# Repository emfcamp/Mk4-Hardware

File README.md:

Hardware
========

Hardware for the TiLDA Mkδ Badge for [Electromagnetic Field
2018](https://www.emfcamp.org).

Key Specs
---------
* TBD
*
*

License
-------
Copyright Electromagnetic Field Ltd. 2017

This documentation describes Open Hardware and is licensed under the
CERN OHL v. 1.2.  You may redistribute and modify this documentation
under the terms of the CERN OHL v.1.2. (http://ohwr.org/cernohl or the
LICENSE file in this repository). This documentation is distributed
WITHOUT ANY EXPRESS OR IMPLIED WARRANTY, INCLUDING OF MERCHANTABILITY,
SATISFACTORY QUALITY AND FITNESS FOR A PARTICULAR PURPOSE. Please see
the CERN OHL v.1.2 for applicable conditions.

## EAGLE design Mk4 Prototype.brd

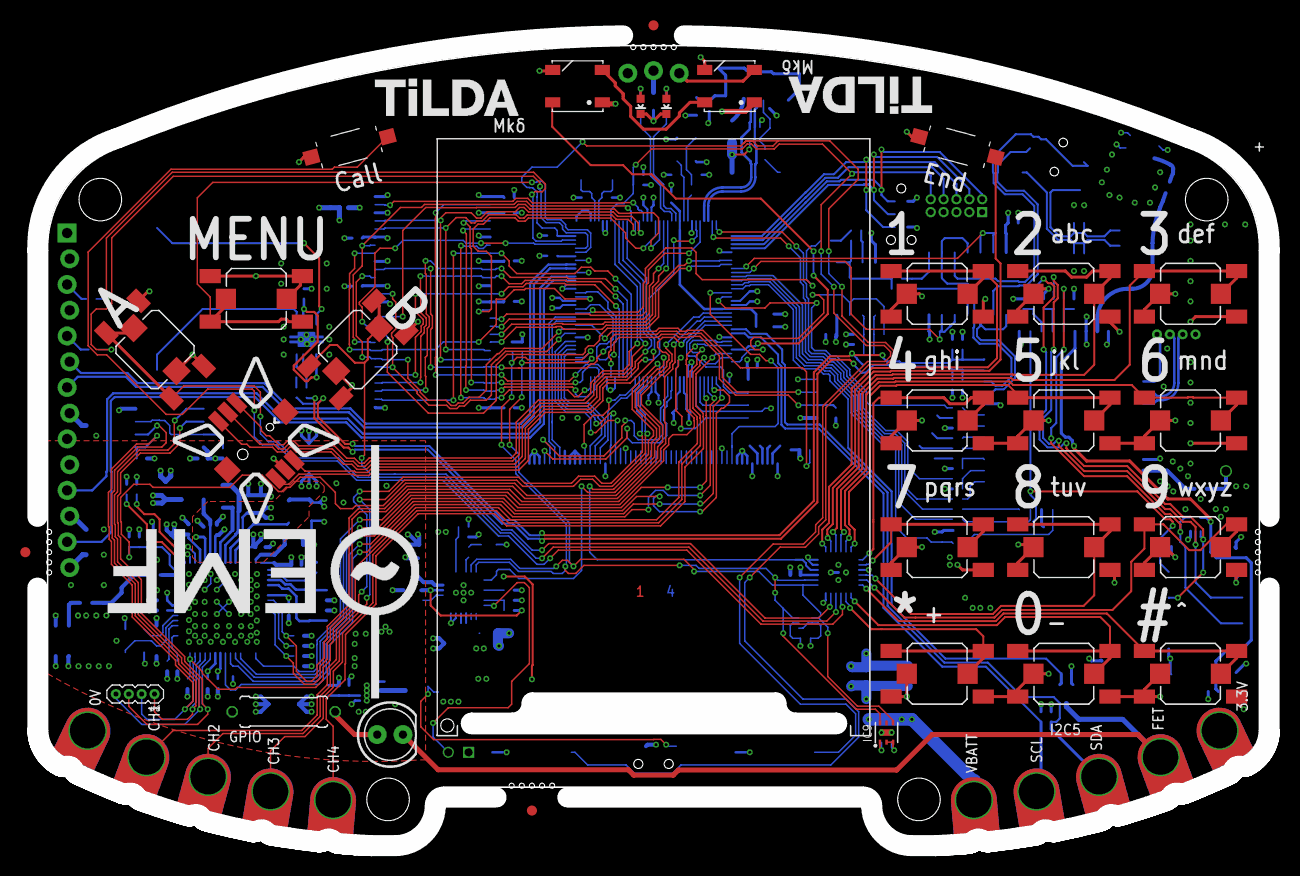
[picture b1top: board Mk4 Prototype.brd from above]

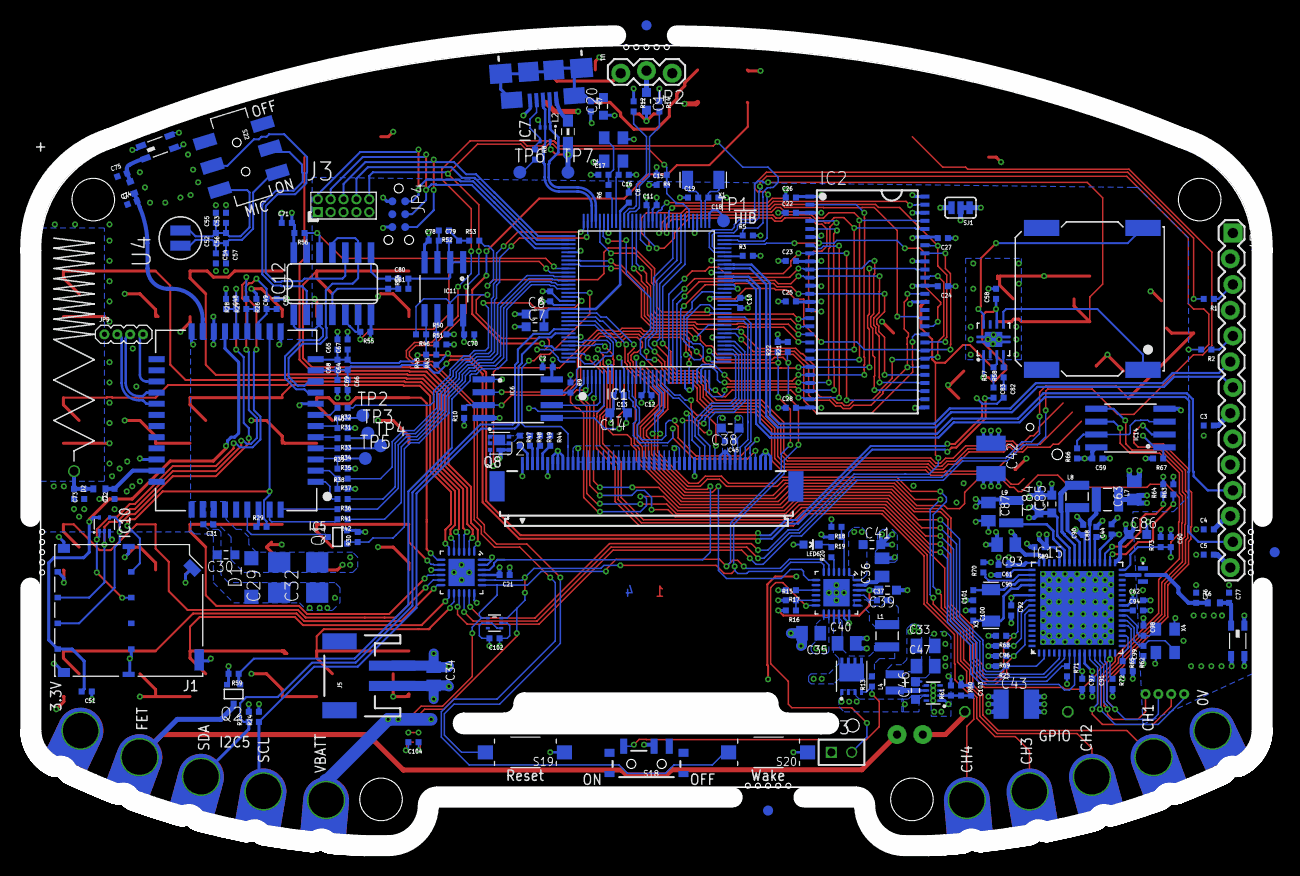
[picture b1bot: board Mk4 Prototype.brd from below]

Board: 4 copper layers, 121.6 x 80.0 mm, 278 parts (242 on the bottom side), 234 nets.

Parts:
ANT1, ANT2: 2450AT18D0100
ARTWORK1: ARTWORK_JOYSTICK; TILDA_ARTWORK_JOYSTICK
ARTWORK2: ARTWORK_KEYPAD; TILDA_ARTWORK_KEYPAD
BATT: 1000mAh JST-PH; BATTERY-32X50
C1, C7, C14, C41, C86: 0603/1u/6V3/X5R; C0603K-SMALL
C2, C3, C4, C5, C8, C9, C10, C11, C12, C13, C15, C21, C22, C23, C24, C25, C26, C27, C28, C31, C44, C45, C51, C58, C59, C60, C61, C62, C70, C71, C80, C81, C91, C92, C94, C95, C96, C97, C102, C104: 0402/100n/10V/X5R; C0402-SMALLER
C6: 0603/2u2/6V3/X5R; C0603K-SMALL
C16, C17, C18, C19, C98, C99, C100, C101: 0402/12p/50V/C0G; C0402-SMALLER
C20: 0603/3n3/50V/X7R; C0603K-SMALL
C29, C32: 1411/100u/10V/Tant; CT3528
C30, C38, C39, C46: 0603/4u7/10V/X5R; C0603K-SMALL
C33, C34, C35, C36, C40, C47, C63, C87, C93: 0805/10u/10V/X5R; C0805-N
C37: 0402/47n/10V/X5R; C0402-SMALLER
C42, C43: 1210/100u/6V3/X5R; C1210K
C48, C49, C50: 0402/22p/10V/C0G; C0402-SMALLER
C52, C54, C55, C64, C66, C67: 0402/33p/50V/C0G; C0402-SMALLER
C53, C56, C57, C65, C68, C69: 0402/10p/50V/C0G; C0402-SMALLER
C72, C73, C74, C75, C76, C77: C0402-SMALLER
C78: 0402/1n/10V/X5R; C0402-SMALLER
C79: 0402/2n2/10V/X5R; C0402-SMALLER
C82, C83: 0402/220n/6V/X5R; C0402-SMALLER
C84, C85: 0603/22u/4V/X5R; C0603K-SMALL
C88, C89, C90: 0402/4u7/6V3/X5R; C0402-SMALLER
C103: 0402/120p/50V/C0G; C0402-SMALLER
D1: MMSZ5231BT1G; SOD123
D2: LXES15AAA1-153; R0402-SMALLER
FID1, FID2, FID3, FID4, FID5, FID6: FIDUCIAL1X2.5-STOP; FIDUCIAL-1X2.5-STOP
FL1: DEA202450BT-1294C1-H; DEA202450BT
IC1: MSP432E401; QFP128-0.4
IC2: AS4C4M16SA-7TCN; TSOP54-400
IC3: TPS62822DLCR; VSON-HR
IC4: TCA9555RGER; QFN-24
IC5: SIM800C
IC6: SST26VF016B-104I/SM; SO08-EIAJ
IC7, IC10: TPD3E001DRL; DRL-5
IC8: BQ25601; QFN-24
IC9: OPT3001; USON-6
IC11: LMV358ID; SO08
IC12: SN74HC4066D; SO14
IC13: TPA2006D1; VSON-8
IC14: MX25R1635FM1IL0; SO08-EIAJ
IC15: CC3120R; VQFN-64
J1: 78723-1001; MSIM-MOLEX-LWK
J2: ER-CON50HT-1; FH12-50S-0.5SH
J3: 2x5 1.27mm; PINHEAD_2X05_127
J4: GSM-COIL-ANT; GSM-ANTENNA
J5: S2B-PH-SM4-TB(LF)(SN); JST-2-SMD
JP2: 1x03; 1X03_LOCK
JP3: 1x02 2MM; 1X02_2MM
JP4: TC2030-MCP-NL
JP7: 1x14; 1X14_LOCK
JP8, JP9: 1x04_1.27MM; 1X04-1.27MM
L1: SRN2512-2R2M; 1008
L2: BLM18KG121TN1D; WUERTH-0805
L3, L5, L6: 0402/0R/5%; L0402
L4: DFE201610E-R47M=P2; 0806
L7, L9: LQM2HPN2R2MG0L; 1008
L8: LQM2HPN1R0MG0L; 1008
LAYERS1: LAYER_NUMBRS_4_SMALL; LAYER_NUMBERS_4_SMALL
LCD: ER-TFT024-3
LED1, LED2: WS2812B
LED3, LED6: 0603 RED; LED-0603-CORRECT
LED4: 0603 GREEN; LED-0603-CORRECT
LED5: LED 5MM; LED5MM
LOGO1: EMFLOGO-BOTH; EMFLOGO
PCB: TiLDA Mk4 PCB; TILDA_MK4_OUTLINE
Q1, Q2: 2N7002PW; SC70-3-R
Q3: CSD25402Q3A; Q3A
Q8: CSD13202Q2; Q2
R1, R2, R31, R32, R33, R34, R35, R36, R37, R41, R42: 0402/1K/5%; R0402-SMALLER
R3: 0402/4K87/5%; R0402-SMALLER
R4, R9, R10, R13, R15, R16, R18, R19, R20, R43, R45, R46, R54, R55, R56, R59, R62, R66: 0402/10K/5%; R0402-SMALLER
R5, R7: 0402/1M/5%; R0402-SMALLER
R6, R12, R17: 0402/2K/5%; R0402-SMALLER
R8: 0402/100R/5%; R0402-SMALLER
R11: 0309/10
R14, R21, R22, R23, R24, R29: 0402/4K7/5%; R0402-SMALLER
R25, R30, R63, R64, R65, R67, R68, R69, R70, R71, R72, R73: 0402/100K/5%; R0402-SMALLER
R26, R27, R28: 0402/51R/5%; R0402-SMALLER
R38, R39, R40: 0402/5K6/5%; R0402-SMALLER
R44, R47, R48, R49: 0402/12R/5%; R0402-SMALLER
R50, R51: 0402/22K/5%; R0402-SMALLER
R52: 0402/14K7/5%; R0402-SMALLER
R53: 0402/7K87/5%; R0402-SMALLER
R57, R58: 0402/150K/1%; R0402-SMALLER
R60: 0402/732K/5%; R0402-SMALLER
R61: 0402/162K/5%; R0402-SMALLER
S1, S2, S3, S4, S5, S6, S7, S8, S9, S10, S11, S12, S13, S14, S15: SKPMAPE010; SKPMAPE010-COMBINED
S16, S17, S19, S20: 3X6X2.5; TACTILE_SWITCH_SMD_3X6X2.5H
S18: CUS-12TB; SWITCH-SPST-SMD-A
S22: AYZ0202AGRLC; AYZ-JS-COMBINED
SJ1: Amp Power Select; SJ_3
SW1: JOYSTICK; JOYSTICK_MULTICOMP_NOSILK
TP1, TP2, TP3, TP4, TP5, TP6, TP7: TP; B1,27
U1: ZX62-B-5PA(33); USB-AB-MICRO-SMD_LWK
U2: TMP102; SOT563
U4: MIC-4MM; MIC-SMD-4MM
U5: LDMS1540S-01-R8-0.8-R; SPEAKER-15MM-SMD
X1, X3: ABS07-32.768KHZ-T; RESONATOR_EPSON_FC_145
X2: ABM8G-25.000MHZ-B4Y-T; CRYSTAL-3.2-2.5
X4: ABM8-40.000MHZ-10-1-U-T; CRYSTAL-3.2-2.5

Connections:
3V3: C2.2, C3.2, C4.2, C9.2, C10.2, C11.2, C12.2, C13.2, C14.2, C21.2, C22.2, C23.2, C24.2, C25.2, C26.2, C27.2, C28.2, C33.1, C38.2, C42.2, C43.2, C45.2, C47.1, C59.2, C70.2, C71.2, C88.1, C89.1, C90.1, C91.1, C92.1, C93.1, C102.1, C103.1, C104.1, IC1.7, IC1.8, IC1.9, IC1.16, IC1.26, IC1.28, IC1.39, IC1.47, IC1.51, IC1.52, IC1.68, IC1.69, IC1.79, IC1.90, IC1.101, IC1.113, IC1.122, IC2.1, IC2.3, IC2.9, IC2.14, IC2.27, IC2.43, IC2.49, IC4.21, IC6.8, IC9.1, IC11.8, IC12.14, IC14.8, IC15.10, IC15.37, IC15.39, IC15.44, IC15.47, IC15.54, J2.1, J2.7, J2.8, J2.9, J2.35, J2.40, J2.41, J2.42, J3.1, JP4.1, JP7.8, JP7.12, L4.2, PCB.3V3, R4.2, R5.2, R9.1, R10.1, R11.2, R21.2, R22.2, R23.2, R24.2, R50.2, R56.2, R60.1, R66.1, R67.2, R68.2, R69.2, R73.2, SJ1.1, SW1.COM, U2.5
3V3_POE: C5.2, JP7.14
!HIB: IC1.65, TP1.TP
!RESET: C15.2, IC1.70, J3.10, R4.1, S19.2
!WAKE: IC1.64, R5.1, S20.2
AIN0_ADC_X: IC1.13, J2.46
AIN1_ADC_Y: IC1.12, J2.47
AIN4_SPK_ADC: IC1.128, IC11.7, R46.2
AIN5_CH3: IC1.127, PCB.CH2
AMP_IN_N: IC13.4, R58.2
AMP_IN_P: IC13.3, R57.2
AMP_IN_R_N: C82.1, R58.1
AMP_IN_R_P: C83.1, R57.1
AMP_VDD: C58.1, IC13.1, IC13.6, SJ1.2
BQ_!CE: IC8.9, R17.1
BQ_!INT: IC1.14, IC8.7
BQ_!QON: IC8.12, JP3.2
BQ_PMID: C36.1, IC8.23
BQ_PSEL: IC8.2, R18.1, R19.1
BQ_REGN: C39.2, IC8.22, R16.2
BQ_STAT: IC8.4, R20.1
BQ_STAT_R: LED6.C, R20.2
BQ_SW: C37.2, IC8.19, IC8.20, L1.1
BQ_TS: IC8.11, R15.2, R16.1
BTN_1: IC4.1, S1.2, S1.B1, S1.B2
BTN_2: IC4.3, S2.2, S2.B1, S2.B2
BTN_3: IC4.4, S3.2, S3.B1, S3.B2
BTN_4: IC4.7, S4.2, S4.B1, S4.B2
BTN_5: IC4.6, S5.2, S5.B1, S5.B2
BTN_6: IC4.5, S6.2, S6.B1, S6.B2
BTN_7: IC4.8, S7.2, S7.B1, S7.B2
BTN_8: IC4.10, S8.2, S8.B1, S8.B2
BTN_9: IC4.11, S9.2, S9.B1, S9.B2
BTN_10: IC4.14, S10.2, S10.B1, S10.B2
BTN_11: IC4.13, S11.2, S11.B1, S11.B2
BTN_12: IC4.12, S12.2, S12.B1, S12.B2
BTN_A: IC4.16, S13.2, S13.B1, S13.B2
BTN_B: IC4.17, S15.2, S15.B1, S15.B2
BTN_CALL: IC4.15, S16.2
BTN_END: IC4.2, S17.2
BTN_MENU: IC1.60, S14.2, S14.B1, S14.B2
BTST: C37.1, IC8.21
BT_ANT: C74.2, IC5.20, L5.1
BT_ANT_L: ANT2.1, C75.2, L5.2
CC_!HIB: IC1.124, IC15.2, R25.1
CC_!RESET: C60.2, IC1.118, IC15.32, R73.1
CC_!RTS: IC15.50, R70.1
CC_IRQ: IC1.123, IC15.15, R72.1
CC_RCT_XTAL_N: C100.2, IC15.52, X3.P$1
CC_RESERVED@19: IC15.19, R65.1
CC_RTC_XTAL_P: C101.2, IC15.51, X3.P$2
CC_WLAN_XTAL_: C99.2, IC15.22, X4.3
CC_WLAN_XTAL_P: C98.2, IC15.23, X4.1
CH4: IC1.126, PCB.CH1
DCDC_ANA_SW: IC15.38, L7.2
DCDC_DIG_SW: IC15.43, L9.2
DCDC_PA_SW_N: IC15.41, L8.1
DCDC_PA_SW_P: IC15.40, L8.2
EN0RXI_N: IC1.53, JP7.13
EN0RXI_P: IC1.54, JP7.11
EN0TXO_N: IC1.56, JP7.7
EN0TXO_P: IC1.57, JP7.6
ETHLED0: IC1.63, R1.2
ETHLED0_R: JP7.3, R1.1
ETHLED1: IC1.61, R2.2
ETHLED1_R: JP7.5, R2.1
FET: IC1.110, Q2.1, R59.1
FET_OUT: LED5.K, PCB.FET, Q2.3
FLASH_!CS: IC14.1, IC15.14, JP8.2, R67.1
FLASH_CLK: IC14.6, IC15.11, JP8.3
FLASH_MISO: IC14.2, IC15.13, JP8.1
FLASH_MOSI: IC14.5, IC15.12, JP8.4
FLASH_PU: IC14.3, IC14.7, R66.2
GMS_ANT_L: C73.2, D2.1, J4.ANT, L3.2
GND: ANT1.2, ANT1.3, ANT1.4, ANT2.2, ANT2.3, ANT2.4, C1.2, C2.1, C3.1, C4.1, C5.1, C6.1, C7.1, C8.1, C9.1, C10.1, C11.1, C12.1, C13.1, C14.1, C15.1, C16.1, C17.1, C18.1, C19.1, C20.1, C21.1, C22.1, C23.1, C24.1, C25.1, C26.1, C27.1, C28.1, C29.-, C30.1, C31.1, C32.-, C33.2, C34.2, C35.2, C36.2, C38.1, C39.1, C40.2, C41.2, C42.1, C43.1, C44.2, C45.1, C46.2, C47.2, C48.1, C49.1, C50.1, C51.1, C53.2, C54.2, C55.2, C57.2, C58.2, C59.1, C60.1, C61.2, C62.2, C63.2, C65.2, C66.2, C67.2, C69.2, C70.1, C71.1, C72.1, C73.1, C74.1, C75.1, C76.1, C77.1, C78.1, C84.2, C85.2, C86.2, C87.2, C88.2, C89.2, C90.2, C91.2, C92.2, C93.2, C94.2, C95.2, C96.2, C97.2, C98.1, C99.1, C100.1, C101.1, C102.2, C104.2, D1.A, D2.2, FL1.GND@2, FL1.GND@4, IC1.10, IC1.17, IC1.48, IC1.55, IC1.58, IC1.80, IC1.114, IC2.6, IC2.12, IC2.28, IC2.41, IC2.46, IC2.52, IC2.54, IC3.3, IC3.5, IC4.9, IC4.18, IC4.23, IC4.24, IC4.25, IC5.8, IC5.13, IC5.19, IC5.21, IC5.27, IC5.30, IC5.31, IC5.33, IC5.36, IC5.37, IC6.4, IC7.3, IC8.17, IC8.18, IC8.25, IC9.2, IC9.3, IC9.PAD, IC10.3, IC11.4, IC12.7, IC13.7, IC13.PAD, IC14.4, IC15.PAD, J1.C4, J1.C5, J1.GND1, J1.GND2, J1.GND3, J1.GND4, J1.GND5, J1.GND6, J2.6, J2.11, J2.12, J2.13, J2.14, J2.15, J2.16, J2.17, J2.18, J2.19, J2.20, J2.21, J2.22, J2.23, J2.24, J2.25, J2.26, J2.27, J2.28, J2.29, J2.30, J2.31, J2.32, J2.43, J2.48, J2.49, J2.50, J3.3, J3.5, J3.9, J5.1, JP2.1, JP3.1, JP4.5, JP7.1, JP7.2, JP7.4, JP9.1, LED1.3, LED2.3, LED3.C, LED4.C, PCB.GND, Q1.2, Q2.2, Q8.4, Q8.EP2, R3.2, R7.2, R15.1, R17.2, R19.2, R25.2, R30.2, R38.2, R39.2, R40.2, R51.2, R55.1, R59.2, R61.2, R62.2, R63.2, R64.2, R65.2, R70.2, R71.2, R72.2, S1.1, S1.A1, S1.A2, S2.1, S2.A1, S2.A2, S3.1, S3.A1, S3.A2, S4.1, S4.A1, S4.A2, S5.1, S5.A1, S5.A2, S6.1, S6.A1, S6.A2, S7.1, S7.A1, S7.A2, S8.1, S8.A1, S8.A2, S9.1, S9.A1, S9.A2, S10.1, S10.A1, S10.A2, S11.1, S11.A1, S11.A2, S12.1, S12.A1, S12.A2, S13.1, S13.A1, S13.A2, S14.1, S14.A1, S14.A2, S15.1, S15.A1, S15.A2, S16.1, S17.1, S18.2, S19.1, S20.1, U1.GND, U2.2, U2.4, X2.2, X2.4, X4.2, X4.4
GSM_ANT: C72.2, IC5.32, L3.1
I2C5_EXT_SCL: IC1.121, PCB.SCL, R24.1
I2C5_EXT_SDA: IC1.120, PCB.SDA, R23.1
I2C9_SCL: IC1.33, IC4.19, IC8.5, IC9.4, R22.1, U2.1
I2C9_SDA: IC1.34, IC4.20, IC8.6, IC9.6, R21.1, U2.6
JOY_CEN: IC1.72, SW1.CTR
JOY_DOWN: IC1.74, SW1.D
JOY_LEFT: IC1.73, SW1.C
JOY_RIGHT: IC1.91, SW1.B
JOY_UP: IC1.71, SW1.A
LCD_!RST: IC1.111, J2.10
LCD_DCX: IC1.20, J2.36
LCD_TEAR: IC1.21, J2.39
LED1: IC1.86, R12.2
LED1_R: LED3.A, R12.1
LED2: IC1.85, R14.2
LED2_R: LED4.A, R14.1
LED5_R: LED5.A, R11.1
LEDK: Q8.1, Q8.2, Q8.5, Q8.6, Q8.EP1, R44.1, R47.1, R48.1, R49.1
LEDK1: J2.2, R47.2
LEDK2: J2.3, R48.2
LEDK3: J2.4, R49.2
LEDK4: J2.5, R44.2
MIC_MUX_N: IC5.10, IC12.9, IC12.11
MIC_MUX_P: IC5.9, IC12.1, IC12.3
MIC_N: C52.2, C53.1, C55.1, C56.2, S22.6, U4.-
MIC_P: C52.1, C54.1, C56.1, C57.1, S22.3, U4.+
MIC_PWM_AMP: C79.1, C80.2, C81.2, IC11.1, IC11.2
MIC_PWM_AMP_+: C78.2, IC11.3, R52.2
MIC_PWM_N: C80.1, IC12.8, R54.1
MIC_PWM_P: C81.1, IC12.4, R54.2
MIC_PWM_R: C79.2, R52.1, R53.1
MIC_SWITCHED_N: IC12.10, S22.5
MIC_SWITCHED_P: IC12.2, S22.2
MUX_A: IC1.105, IC12.12, IC12.13, R56.1
MUX_B: IC1.106, IC12.5, IC12.6, R55.2
NETLIGHT_R: IC5.41, R42.2
OSC0: C16.2, IC1.88, X2.1
OSC1: IC1.89, R6.1
OSC1_R: C17.2, R6.2, X2.3
POWER_SWITCH: Q3.4, R13.1, S18.3
PWM0_LCD_BLIGHT: IC1.42, Q8.3
PWM3_MIC_PWM: IC1.45, R53.2
PWR_KEY_FET: IC5.39, Q1.3
RBIAS+: IC1.59, R3.1
SDRAM_!CAS: IC1.83, IC2.17
SDRAM_!CS: IC1.103, IC2.19
SDRAM_!RAS: IC1.84, IC2.18
SDRAM_!WE: IC1.92, IC2.16
SDRAM_A0: IC1.29, IC2.2, IC2.23
SDRAM_A1: IC1.30, IC2.4, IC2.24
SDRAM_A2: IC1.31, IC2.5, IC2.25
SDRAM_A3: IC1.32, IC2.7, IC2.26
SDRAM_A4: IC1.22, IC2.8, IC2.29
SDRAM_A5: IC1.23, IC2.10, IC2.30
SDRAM_A6: IC1.24, IC2.11, IC2.31
SDRAM_A7: IC1.25, IC2.13, IC2.32
SDRAM_A8: IC1.40, IC2.33, IC2.42
SDRAM_A9: IC1.41, IC2.34, IC2.44
SDRAM_A10: IC1.50, IC2.22, IC2.45
SDRAM_A11: IC1.49, IC2.35, IC2.47
SDRAM_A12: IC1.75, IC2.36, IC2.48
SDRAM_BA0: IC1.76, IC2.20, IC2.50
SDRAM_BA1: IC1.77, IC2.21, IC2.51
SDRAM_CKE: IC1.104, IC2.37
SDRAM_CLK: IC1.62, IC2.38
SDRAM_D15: IC1.78, IC2.53
SDRAM_DQMH: IC1.82, IC2.39
SDRAM_DQML: IC1.81, IC2.15
SIM_CLK: IC10.2, J1.C3, R27.2
SIM_CLK_R: C49.2, IC5.16, R27.1
SIM_CTS: R34.1, TP4.TP
SIM_CTS_R: IC5.4, R34.2
SIM_DATA: IC10.1, J1.C7, R26.2
SIM_DATA_R: C50.2, IC5.15, R26.1
SIM_DCD: R33.1, TP3.TP
SIM_DCD_R: IC5.5, R33.2
SIM_DET: IC5.14, J1.C8, R29.2
SIM_DTR: R31.1, TP2.TP
SIM_DTR_R: IC5.6, R31.2, R40.1
SIM_D_N: IC5.26, JP9.2
SIM_D_P: IC5.25, JP9.3
SIM_NETLIGHT: IC1.108, R42.1
SIM_PWR_KEY: IC1.109, Q1.1, R30.1
SIM_RI_R: IC5.7, R32.2
SIM_RST: IC10.4, J1.C2, R28.2
SIM_RST_R: C48.2, IC5.17, R28.1
SIM_RTS: R35.1, TP5.TP
SIM_RTS_R: IC5.3, R35.2, R39.1
SIM_RXD_R: IC5.2, R37.2, R38.1
SIM_STATUS: IC1.107, R41.1
SIM_STATUS_R: IC5.42, R41.2
SIM_TXD_R: IC5.1, R36.2
SIM_VBUS: IC5.24, JP9.4
SIM_VDD: C51.2, IC5.18, IC10.5, J1.C1
SOP0: IC15.35, R64.1
SOP1: IC15.34, R63.1
SOP2: IC15.21, R62.1
SPK_AMP_N: IC13.8, U5.-
SPK_AMP_P: IC13.5, U5.+
SPK_N: C64.2, C65.1, C67.1, C68.2, C82.2, IC5.12, R43.1
SPK_P: C64.1, C66.1, C68.1, C69.1, C83.2, IC5.11, R45.1
SPK_R_N: IC11.5, R45.2, R46.1
SPK_R_P: IC11.6, R43.2, R50.1, R51.1
SSI0_LCD_CLK: IC1.35, J2.37
SSI0_LCD_CS: IC1.36, J2.38
SSI0_LCD_MISO: IC1.38, J2.33
SSI0_LCD_MOSI: IC1.37, J2.34
SSI2_CC_!CS: IC1.3, IC15.8
SSI2_CC_CLK: IC1.4, IC15.5
SSI2_CC_MISO: IC1.1, IC15.7, R71.1
SSI2_CC_MOSI: IC1.2, IC15.6
SSI3_CLK: IC1.5, IC6.6
SSI3_DAT0: IC1.11, IC6.5
SSI3_DAT1: IC1.27, IC6.2
SSI3_DAT2: IC1.46, IC6.3, R10.2
SSI3_DAT3: IC1.119, IC6.7, R9.2
SSI3_FSS: IC1.6, IC6.1
SW: IC3.6, L4.1
T3CCPO_WS2812: IC1.125, LED1.4
TCA_INT: IC1.15, IC4.22
TCK_SWCLK: IC1.100, J3.4, JP4.4
TDI: IC1.98, J3.8
TDO_SWO: IC1.97, J3.6, JP4.6
TMS_SWDIO: IC1.99, J3.2, JP4.2
TPS_FB: C103.2, IC3.2, R60.2, R61.1
T_X: IC1.43, J2.44
T_Y: IC1.44, J2.45
UART1_SIM_RI: IC1.112, R32.1
UART1_SIM_RX: IC1.95, R36.1
UART1_SIM_TX: IC1.96, R37.1
UART3_CC_RX: IC1.116, IC15.55, R68.1
UART3_CC_TX: IC1.117, IC15.57, R69.1
UART5_EXT_RX: IC1.18, PCB.CH3
UART5_EXT_TX: IC1.19, PCB.CH4
USB_D_N: IC1.93, IC7.1, U1.D-
USB_D_P: IC1.94, IC7.2, U1.D+
USB_ID: R8.2, TP6.TP
USB_ID_R: IC7.4, R8.1, U1.ID
USB_SHIELD: C20.2, R7.1, U1.SHIELD, U1.SHIELD@0, U1.SHIELD@1, U1.SHIELD@2, U1.SHIELD@3, U1.SHIELD@5
VBAT: C34.1, C35.1, IC8.13, IC8.14, J5.2
VBATT: C1.1, C29.+, C30.2, C31.2, C32.+, C46.1, D1.C, IC3.1, IC3.7, IC5.34, IC5.35, JP2.2, LED1.1, LED2.1, Q3.1, Q3.2, Q3.3, SJ1.3
VBUS: C41.1, IC7.5, IC8.1, IC8.24, L2.2, LED6.A, TP7.TP
VBUS_L: L2.1, U1.VBUS
VDDC: C6.2, C7.2, C8.2, IC1.87, IC1.115
VDD_ANA: C44.1, C61.1, C62.1, C63.1, IC15.25, IC15.36, IC15.48, L7.1
VDD_DIG_CC: C87.1, C96.1, C97.1, IC15.9, IC15.56, L9.1
VDD_EXT: IC5.40, R29.1
VDD_PA: C84.1, C85.1, C86.1, IC15.33, IC15.42
VDD_PLL: C94.1, IC15.24
VDD_RAM: C95.1, IC15.49
V_UNREG: C40.1, IC8.15, IC8.16, L1.2, PCB.VBATT, Q3.5, Q3.6, Q3.7, Q3.8, Q3.EP, R13.2, R18.2
WFIF_ANT_L: ANT1.1, C77.2, L6.2
WIFI_ANT: C76.2, FL1.OUT, L6.1
WIFI_ANT_F: FL1.IN, IC15.31
WS2812_OUT: JP2.3, LED2.2
WS28212_1: LED1.2, LED2.4
XOSC0: C18.2, IC1.66, X1.P$1
XOSC1: C19.2, IC1.67, X1.P$2

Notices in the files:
Datasheets/MSP432E401/pinout.c:
Copyright (C) 2014 Texas Instruments Incorporated - http://www.ti.com
parts and their libraries:
TiLDA Mk4 Parts: ©2009 ROFA.cz - modified and updated by Robert Darlington ‹rdarlington@gmail.com›
SparkFun-FreqCtrl: Licensing: Creative Commons ShareAlike 4.0 International - https://creativecommons.org/licenses/by-sa/4.0
